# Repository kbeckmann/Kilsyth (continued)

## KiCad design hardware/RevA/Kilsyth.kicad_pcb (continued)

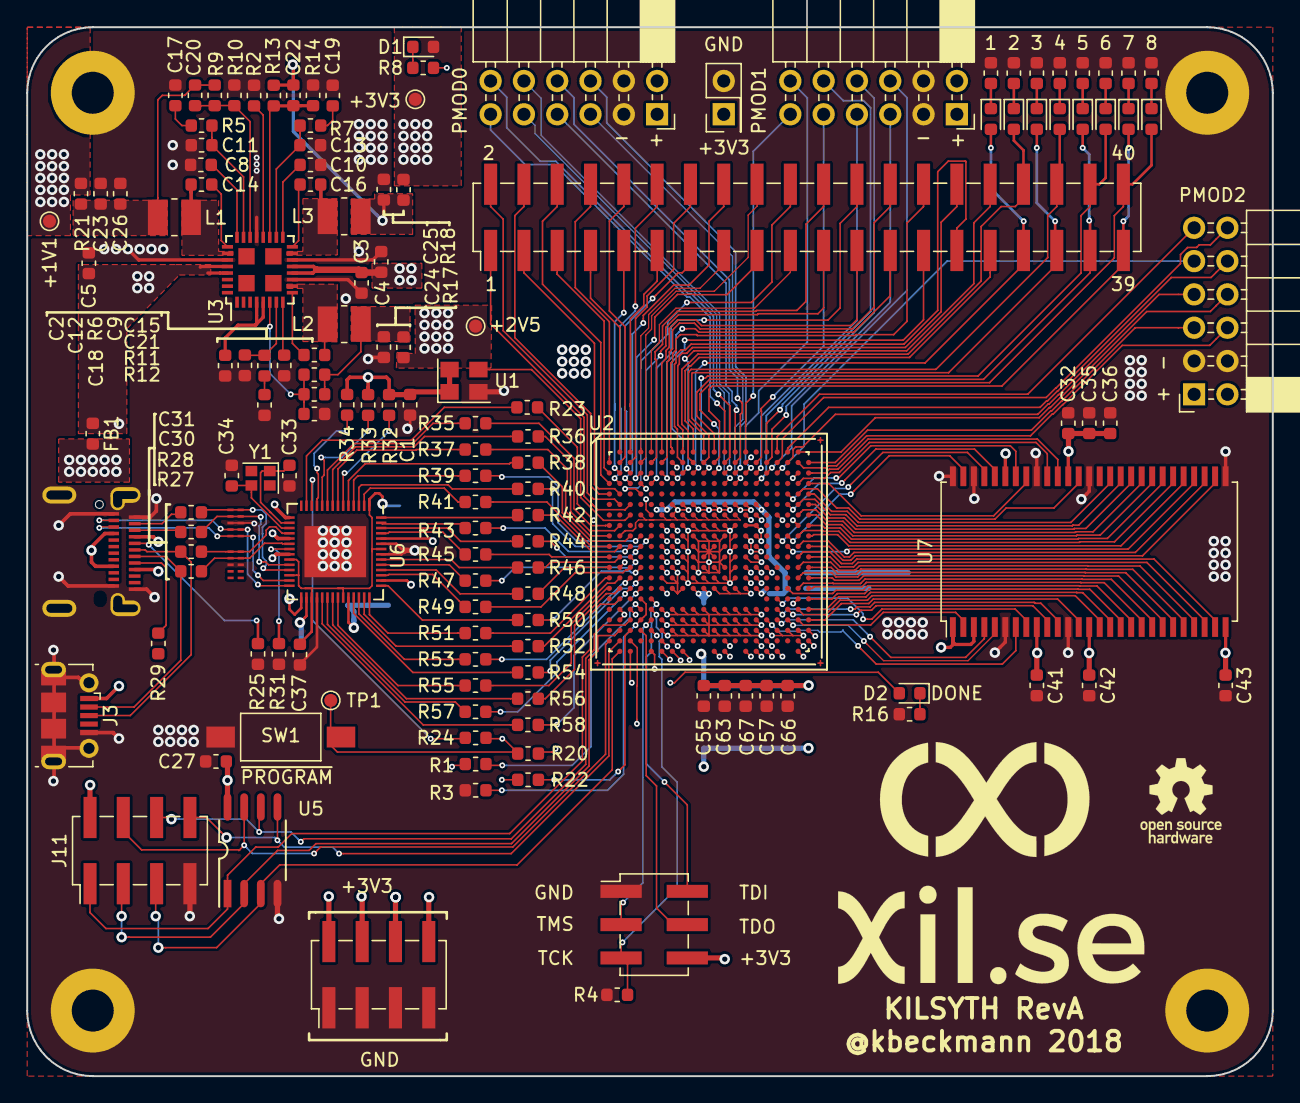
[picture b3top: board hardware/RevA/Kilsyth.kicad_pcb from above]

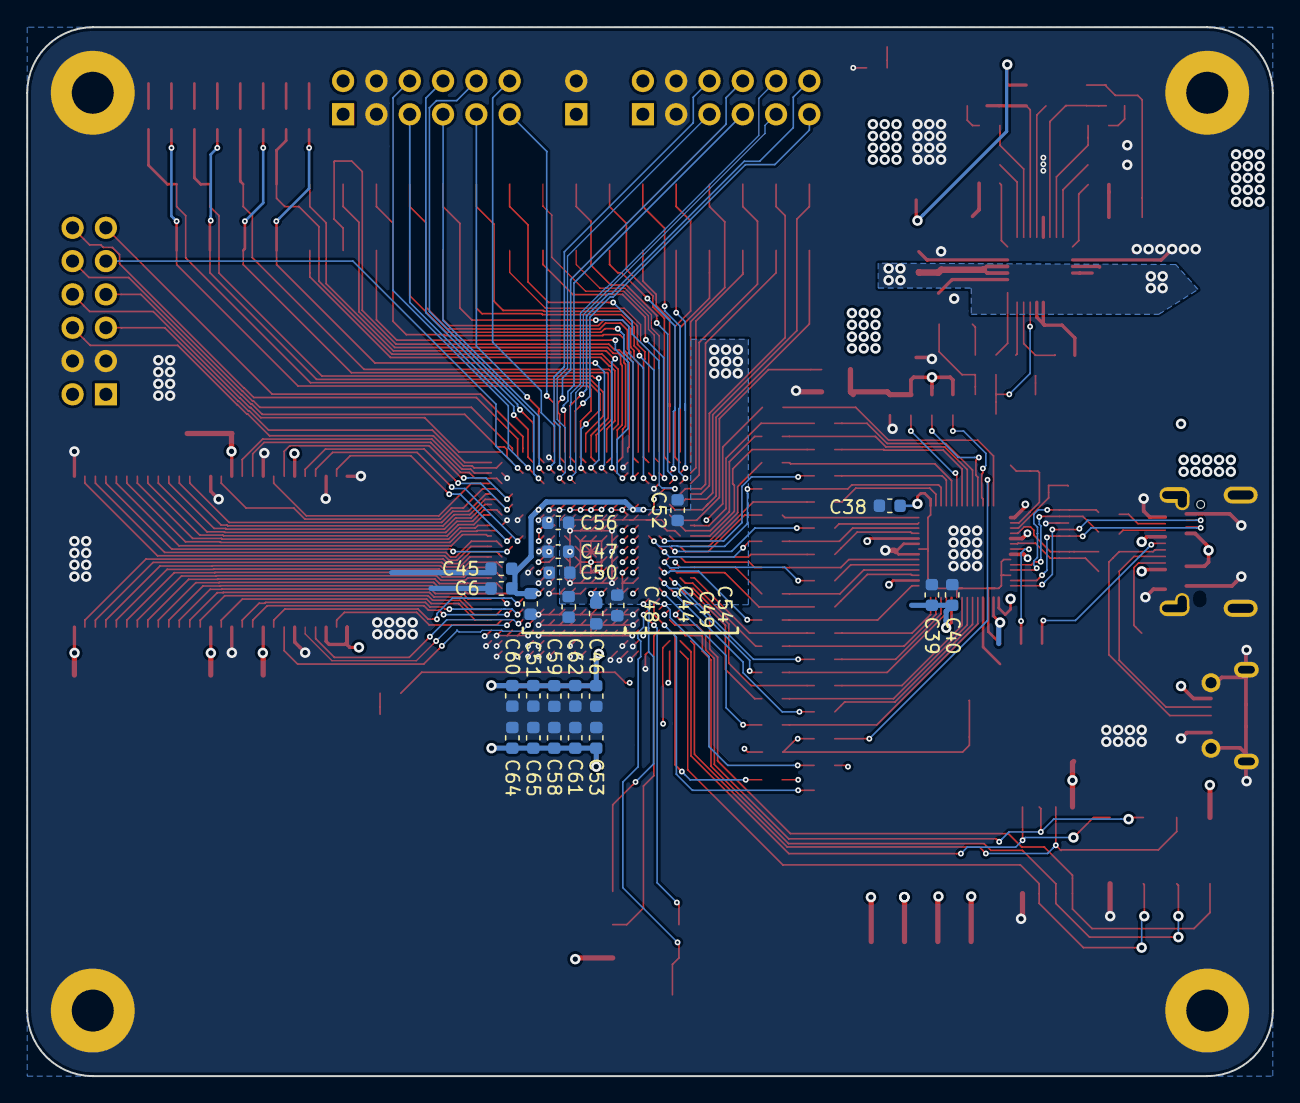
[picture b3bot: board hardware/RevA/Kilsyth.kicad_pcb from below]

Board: 4 copper layers, 95.0 x 80.0 mm, 168 parts (23 on the bottom side), 228 nets.

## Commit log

2018-11-28 Initial commit: WIP
2018-12-02 More progress
2018-12-02 more wip
2018-12-04 fixed footprints
2018-12-04 Hmmmm
2018-12-04 asdf
2018-12-05 Routing
2018-12-06 yarrr. fixed imoprtant pmic bug
2018-12-07 Some progress
2018-12-07 woop
2018-12-07 Keep out
2018-12-08 before r0 hell
2018-12-09 getting somewhere
2018-12-09 Final RevA
2018-12-09 Final touches
2018-12-09 Changed from 4 to 5 mil spacing.. HELL.
2018-12-10 Last minute changes
2018-12-10 Last minute again.. lol
2018-12-10 Final final touches
2018-12-10 Final final final touches
2018-12-10 Minor cosmetic changes and BOM stuff.
2018-12-11 Move files to hardware
2018-12-11 Fix path
2018-12-11 Add errata
2018-12-11 more errata
2018-12-11 add bootloader gateware (blinky)
2018-12-17 Add ibom
2018-12-18 Update pdf
    and delete the plt file, who uses those anyway?
2018-12-18 Don't Look: Bringup
2018-12-18 openocd
2018-12-18 Add BODGE information
2018-12-18 Don't Look: Resave the project
2018-12-18 Don't Look: FT600 bringup baby steps
2018-12-18 Don't Look: fix path
2018-12-18 Add simple openocd script
2018-12-18 Fix paths
2018-12-20 Read all data that comes in
2018-12-21 Loopbackish..
2018-12-21 Clean up the schematic a bit
2018-12-21 Add errata for JTAG connector
2018-12-21 Trellis and cleanup
2018-12-22 Add ft600 trellis project
    It can only receive data. tristate weirdness in nextnpr
2018-12-23 Simple Kilsyth board file and example
    NOTE:
    Needs a hack to migen to pass the --idcode to get a usable bitstream!
2018-12-23 ft600_migen baseline
2018-12-24 Bidirectional transfers seem to work
2018-12-24 blinky: Add simple test
2018-12-25 ft600_migen: This works now and behaves correctly.
    Need to sort out the tristate stuff because this way we
    can't read the data..
2018-12-25 Add gitignore
2018-12-25 Fix tristate stuff
    But it still doesn't seem to work :(
2018-12-25 Add nasty closed source driver example code + mods
2018-12-25 Send counter instead of static words
2018-12-25 Add timing to makefile
    The code is a mess and incorrect though.
2018-12-29 FIFO stream with actual data
2019-01-11 Support all lfe5uXX targets
2019-01-12 Fix multi target
2019-01-12 Pop target
2019-01-12 First steps with python glue
2019-01-12 This will be removed soon..
2019-01-12 Vendor ft60x python driver
2019-01-12 Vendor ft60x sdk
2019-01-12 PATCH: Fix broken linux2 thing?
2019-01-12 PATCH: Fix incorrect type
2019-01-12 PATCH: Add support for 50, 40 MHz in prints
2019-01-12 PATCH: Don't allow empty config, becuase that's stupid
2019-01-12 Fix Makefile
2019-01-12 PATCH: Set empty chip configuration, not Null..
2019-01-12 PATCH: Add support for 50, 40 MHz clock
2019-01-12 PATCH: Reset config to a known state
2019-01-13 Add some nice fifo debug code
2019-01-13 Fixed loopback (almost). Still off by one word.
2019-01-13 Go back to random strings
2019-01-13 improve test
2019-01-13 Getting closer but still off by one
2019-01-13 Make the testbench work again
2019-01-13 Add readme
2019-01-13 Add PI5USB30213A
2019-01-13 Improve testbench
2019-01-16 Work work
2019-01-16 Add all clocks
2019-01-17 Fix the loopback test!
    Now it actually works 100%
    But at 40 and 50 MHz it doesn't. Everything is shifted one clock it seems.
2019-01-17 Cleanup
2019-01-22 add some temporary dualboot stuff
2019-01-23 Add python project (WIP)
2019-02-08 gitignore .pyc
2019-02-08 Fix user_led and pmod0
    Should fix the other pmods too later
2019-02-08 Add early draft of sx1257 communication
2019-02-21 spi_flash_mitm: wip
2019-02-24 Errata: add flash pullups
2019-05-19 SZ1257 RX hack
2019-05-20 Add an AsyncFIFO which solves all the problems
2019-05-21 FIR filtering in python
2019-05-30 Woop! Can send I2C data
2019-05-31 CW signal test
2019-06-01 Works 10/10 times now..
2019-06-01 Make NACK more visible
2019-06-01 Now it works perfectly?
2019-06-01 Make the gap between commands shorter
2019-06-02 optimize a bit
2019-06-03 FIR filter
2019-06-04 WIP: Attempt to make a ft600 module
    Still WIP, getting weird issues
2019-06-04 stuff
2019-06-06 Improve ft600 a lot
2019-06-06 Fix edge case
2019-06-06 add verify tool
2019-06-06 Fix the last issues with Write.
    Now it passes my tests at any rate in any clock domain.
2019-06-07 Loopback works!
2019-06-07 Verify with 16bit values
2019-06-07 SX1257 code import
2019-06-08 Add spi slave example
2019-06-08 Remove stupidness
2019-06-08 Add FT600 module and some applets
    - SX1257 RX applet
    - SPI slate applet
2019-06-08 Add args support for applets
2019-06-09 sx1257: Add support for reva, revb
2019-06-09 Add args to applets
2019-06-11 Support multiple clock domains
2019-06-11 Fix clock domain constraints
2019-06-16 Brutal WIP
2019-06-16 Lots of stuff
2019-06-16 Reworking stuff
2019-06-16 Remove old junk
2019-06-16 Add --skip-prog
2019-06-16 fix ircode
2019-06-16 comment
2019-06-16 Fix ft600.FT600
2019-06-16 Integrate FTD3xx lib and clean up old stuff
2019-06-17 Fix it
2019-06-17 Small fixes
2019-06-17 Add nasty byte swapper
2019-06-18 gitignore
2019-06-21 Rewrite
2019-10-11 Move RevA to its own directory
2019-10-11 RevB initial draft
2019-10-11 Add usb-c-breakout
2019-10-18 Add CircuitPython ECP5Prog
2019-11-06 Add SiPEED config
2020-06-28 Remove idcode hack
2020-06-28 Add SiPEED programmer
2020-06-28 Add logic analyzer (la) applet. 16CH 100MHz
2020-06-28 Sample 8ch at 100MS/s and indicate fifo overflow
2020-06-28 Add unpacker
2020-06-28 2ch @ 400MHz
2020-06-29 Do 400MS/s properly
2020-07-23 Move unpack.c
2020-07-23 Rename kilsyth -> kilsyth_migen
2020-07-24 Initial nMigen port
2020-07-24 Remove junk
2020-07-24 Port nmigen logic analyzer
2020-07-25 Add note about USB2422
2020-07-26 Add setup.py
2020-07-26 Depend on pergola_projects
2020-07-27 vgastream: Initial hacky commit
2020-07-28 vgastream: Capture real DVID now
2020-07-28 vgastream: Stream using v4l2
2020-07-29 ft600_demo: Fix source and sink mode
